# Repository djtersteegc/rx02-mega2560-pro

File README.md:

Mega 2560 Pro Embed version on [AK6DN's DEC RX02 emulator](https://github.com/AK6DN/rx02_emulator) board design and code.  There is a fork of his project at  https://github.com/djtersteegc/rx02_emulator that adds software support for this new board design. This was an exercise in how small I could make it while still using a Mega2560 shield and large'ish 0805 SMD parts for an easy DIY build.  If you are interested in a larger version built on a standard Arduino Mega 2560  with an LCD and buttons so you don't need to pick images via a serial/terminal connection, see my other project at https://github.com/djtersteegc/rx02-emulator-mega-shield.

Here's the two of them side by side on a Heathkit H11 for a size comparison.

See the VCFed thread at https://forum.vcfed.org/index.php?threads/building-the-worlds-currently-smallest-rx02-emulator.1240496/ for discussion or help with this project

# BOM

There is an interactive BOM at https://djtersteegc.github.io/rx02-mega2560-pro/ibom-v1.2.html  It's for a version 1.2 board which is hasn't been produced yet so ignore R32 and D4 which are for a power indicator LED if you are building a version 1.1 board.

C1 and C2 are bulk storage caps for the 5V rail, any value over 33uF should do.  C7 is a 47uF tantalum to prevent sag on the 3.3V rail when hot swapping the SD card since there is usually quite a bit of in rush current.  You can probably do without, especially if you never intend to hot swap since it's not really supported by the firmware.

The SD card connector is commonly available from several different Chinese suppliers and often called "long body", "non popping", or"push pull".  Here's some links on LCSC.

https://www.lcsc.com/product-detail/SD-Card-Connectors_Hanbo-Electronic-SD-112_C961673.html

https://www.lcsc.com/product-detail/SD-Card-Connectors_XUNPU-SD-102_C266602.html

https://www.lcsc.com/product-detail/SD-Card-Connectors_Megastar-ZX-SD-282-8Y_C7419835.html

It should also cross with a Wurth 693063010911 or AMP GSD090012SEU if you want something domestically.

You can also use BSS138 FET's in place of the 2N7002's.

# Assembly

This time around I used the same resistor references as AK6DN's original version so his resistor stuffing table is the same. Most of the resistor footprints should NOT be populated.

| Signal         | Resistor | Value   | Resistor | Value   |
| -------------- | -------- | ------- | -------- | ------- |
| RX_DMA_MODE_H  | R2       | -       | R3       | **390** |
| RX_AC_L        | R4       | **120** | R5       | -       |
| RX_OUT_L       | R6       | -       | R7       | -       |
| RX_SHIFT_L     | R8       | -       | R9       | -       |
| RX_12BIT_L     | R10      | **180** | R23      | **390** |
| RX_DATA_L      | R11      | **180** | R12      | **390** |
| RX_DONE_L      | R13      | -       | R14      | -       |
| RX_XFER_RQST_L | R15      | -       | R16      | -       |
| RX_INIT_L      | R17      | -       | R18      | **390** |
| RX_ERROR_L     | R19      | -       | R20      | -       |
| RX_RUN_L       | R21      | **180** | R22      | **390** |

Assemble the top side first.

Then flip in over and do the bottom.  Followed by the headers and then the 40 pin connector. For the LED's, I first insert them in the PCB, then the PCB in the case, flip it over and support the case ~1mm off the work surface for the LED's to just poke through the top and get a nice reveal. Solder one leg on the LED's, flip it over to check your spacing again, and then solder the other leg.

# Case

Make sure to print two copies of the buttons. Angle the board in connector side first and it should drop in.  It's a snap fit design, so no screws needed to assemble.

# Flashing and Usage

See instructions at https://github.com/djtersteegc/rx02_emulator

# Getting a Board

If you are in the US, hit me up on the [VCFed thread](https://forum.vcfed.org/index.php?threads/building-the-worlds-currently-smallest-rx02-emulator.1240496/) above and if I still have extras, I can drop one in the mail for a couple of bucks. Otherwise, grab the gerbers and fab your own.

# Hardware Revisions

### Version 1.0

Required bodge wires since I failed to pick interrupt enabled pins on the Mega2560 for the RX_INIT and RX_RUN lines when I reamapped the pins to better fit this layout.

### Versions 1.1 (Current)

Working

### Version 1.2 (Not Produced Yet)

Added a power LED

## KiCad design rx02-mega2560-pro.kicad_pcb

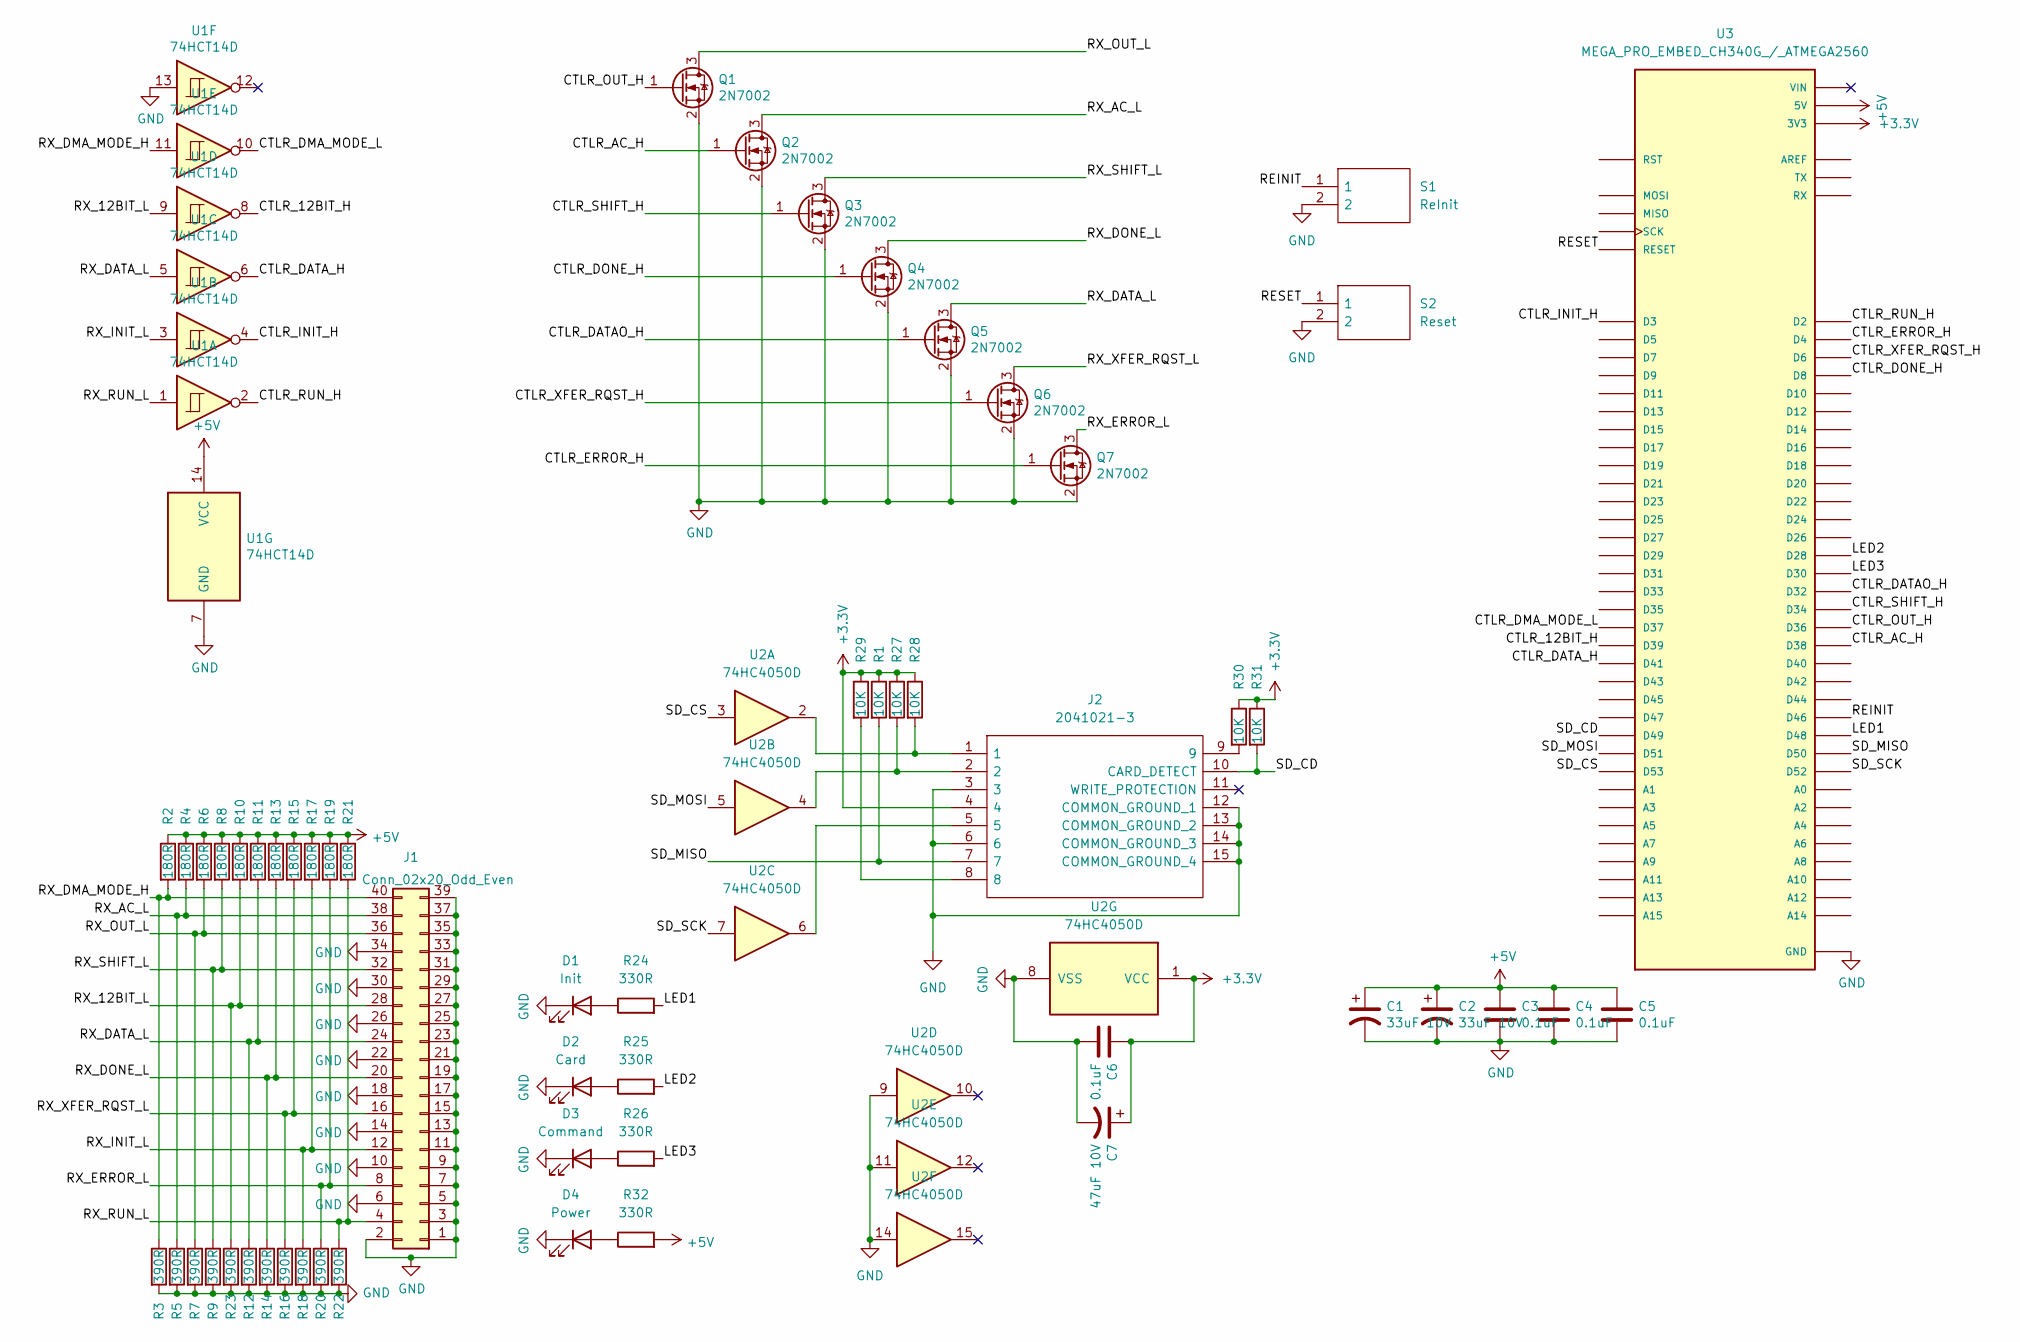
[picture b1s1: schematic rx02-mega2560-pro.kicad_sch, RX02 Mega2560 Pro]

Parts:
C1, C2: 33uF 10V; CP_Elec_5x5.8
C3, C4, C5, C6: 0.1uF; C_0805_2012Metric_Pad1.18x1.45mm_HandSolder
C7: 47uF 10V; CP_EIA-3528-12_Kemet-T_Pad1.50x2.35mm_HandSolder
D1: Init; LED_D3.0mm
D2: Card; LED_D3.0mm
D3: Command; LED_D3.0mm
D4: Power; LED_0805_2012Metric_Pad1.15x1.40mm_HandSolder
J1: Conn_02x20_Odd_Even; IDC-Header_2x20_P2.54mm_Horizontal
J2: 2041021-3; 2041021-3_2; Manufacturer_Part_Number 2041021-3; Mouser Part Number 571-2041021-3
Q1, Q2, Q3, Q4, Q5, Q6, Q7: 2N7002; SOT-23
R1, R27, R28, R29, R30, R31: 10K; R_0805_2012Metric_Pad1.20x1.40mm_HandSolder
R2, R4, R6, R8, R10, R11, R13, R15, R17, R19, R21: 180R; R_0805_2012Metric_Pad1.20x1.40mm_HandSolder
R3, R5, R7, R9, R12, R14, R16, R18, R20, R22, R23: 390R; R_0805_2012Metric_Pad1.20x1.40mm_HandSolder
R24, R25, R26, R32: 330R; R_0805_2012Metric_Pad1.20x1.40mm_HandSolder
S1: ReInit; SW_Push_SPST_NO_Alps_SKRK; Manufacturer_Part_Number SKRKAEE020; Mouser Part Number 688-SKRKAEE020
S2: Reset; SW_Push_SPST_NO_Alps_SKRK; Manufacturer_Part_Number SKRKAEE020; Mouser Part Number 688-SKRKAEE020
U1: 74HCT14D; SOIC-14_3.9x8.7mm_P1.27mm
U2: 74HC4050D; SOIC-16_3.9x9.9mm_P1.27mm
U3: MEGA_PRO_EMBED_CH340G_/_ATMEGA2560; MODULE_MEGA_PRO_EMBED_CH340G___ATMEGA2560; PARTREV 12/May/2017

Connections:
+3V3: C6.1, C7.1, J2.4, R1.1, R27.1, R28.1, R29.1, R30.1, R31.1, U2.1 (VCC), U3.3V3_1 (3V3), U3.3V3_2 (3V3)
+5V: C1.1, C2.1, C3.1, C4.1, C5.1, R2.1, R4.1, R6.1, R8.1, R10.1, R11.1, R13.1, R15.1, R17.1, R19.1, R21.1, R32.2, U1.14 (VCC), U3.5V_1 (5V), U3.5V_2 (5V), U3.5V_3 (5V)
/CTLR_12BIT_H: U1.8, U3.D39
/CTLR_AC_H: Q2.1 (G), U3.D38
/CTLR_DATAO_H: Q5.1 (G), U3.D32
/CTLR_DATA_H: U1.6, U3.D41
/CTLR_DMA_MODE_L: U1.10, U3.D37
/CTLR_DONE_H: Q4.1 (G), U3.D8
/CTLR_ERROR_H: Q7.1 (G), U3.D4
/CTLR_INIT_H: U1.4, U3.D3
/CTLR_OUT_H: Q1.1 (G), U3.D36
/CTLR_RUN_H: U1.2, U3.D2
/CTLR_SHIFT_H: Q3.1 (G), U3.D34
/CTLR_XFER_RQST_H: Q6.1 (G), U3.D6
/LED1: R24.2, U3.D48
/LED2: R25.2, U3.D28
/LED3: R26.2, U3.D30
/REINIT: S1.1, U3.D46
/RESET: S2.1, U3.RESET
/RX_12BIT_L: J1.28, R10.2, R23.1, U1.9
/RX_AC_L: J1.38, Q2.3 (D), R4.2, R5.1
/RX_DATA_L: J1.24, Q5.3 (D), R11.2, R12.1, U1.5
/RX_DMA_MODE_H: J1.40, R2.2, R3.1, U1.11
/RX_DONE_L: J1.20, Q4.3 (D), R13.2, R14.1
/RX_ERROR_L: J1.8, Q7.3 (D), R19.2, R20.1
/RX_INIT_L: J1.12, R17.2, R18.1, U1.3
/RX_OUT_L: J1.36, Q1.3 (D), R6.2, R7.1
/RX_RUN_L: J1.4, R21.2, R22.1, U1.1
/RX_SHIFT_L: J1.32, Q3.3 (D), R8.2, R9.1
/RX_XFER_RQST_L: J1.16, Q6.3 (D), R15.2, R16.1
/SD_CD: J2.10 (CARD_DETECT), R31.2, U3.D49
/SD_CS: U2.3, U3.D53
/SD_MISO: J2.7, R1.2, U3.D50
/SD_MOSI: U2.5, U3.D51
/SD_SCK: U2.7, U3.D52
GND: C1.2, C2.2, C3.2, C4.2, C5.2, C6.2, C7.2, D1.1 (K), D2.1 (K), D3.1 (K), D4.1 (K), J1.1, J1.2, J1.3, J1.5, J1.6, J1.7, J1.9, J1.10, J1.11, J1.13, J1.14, J1.15, J1.17, J1.18, J1.19, J1.21, J1.22, J1.23, J1.25, J1.26, J1.27, J1.29, J1.30, J1.31, J1.33, J1.34, J1.35, J1.37, J1.39, J2.3, J2.6, J2.12 (COMMON_GROUND_1), J2.13 (COMMON_GROUND_2), J2.14 (COMMON_GROUND_3), J2.15 (COMMON_GROUND_4), Q1.2 (S), Q2.2 (S), Q3.2 (S), Q4.2 (S), Q5.2 (S), Q6.2 (S), Q7.2 (S), R3.2, R5.2, R7.2, R9.2, R12.2, R14.2, R16.2, R18.2, R20.2, R22.2, R23.2, S1.2, S2.2, U1.7 (GND), U1.13, U2.8 (VSS), U2.9, U2.11, U2.14, U3.GND_1 (GND), U3.GND_2 (GND), U3.GND_3 (GND)
unnamed: D1.2 (A), R24.1
unnamed: D2.2 (A), R25.1
unnamed: D3.2 (A), R26.1
unnamed: D4.2 (A), R32.1
unnamed: J2.1, R28.2, U2.2
unnamed: J2.2, R27.2, U2.4
unnamed: J2.5, U2.6
unnamed: J2.8, R29.2
unnamed: J2.9, R30.2

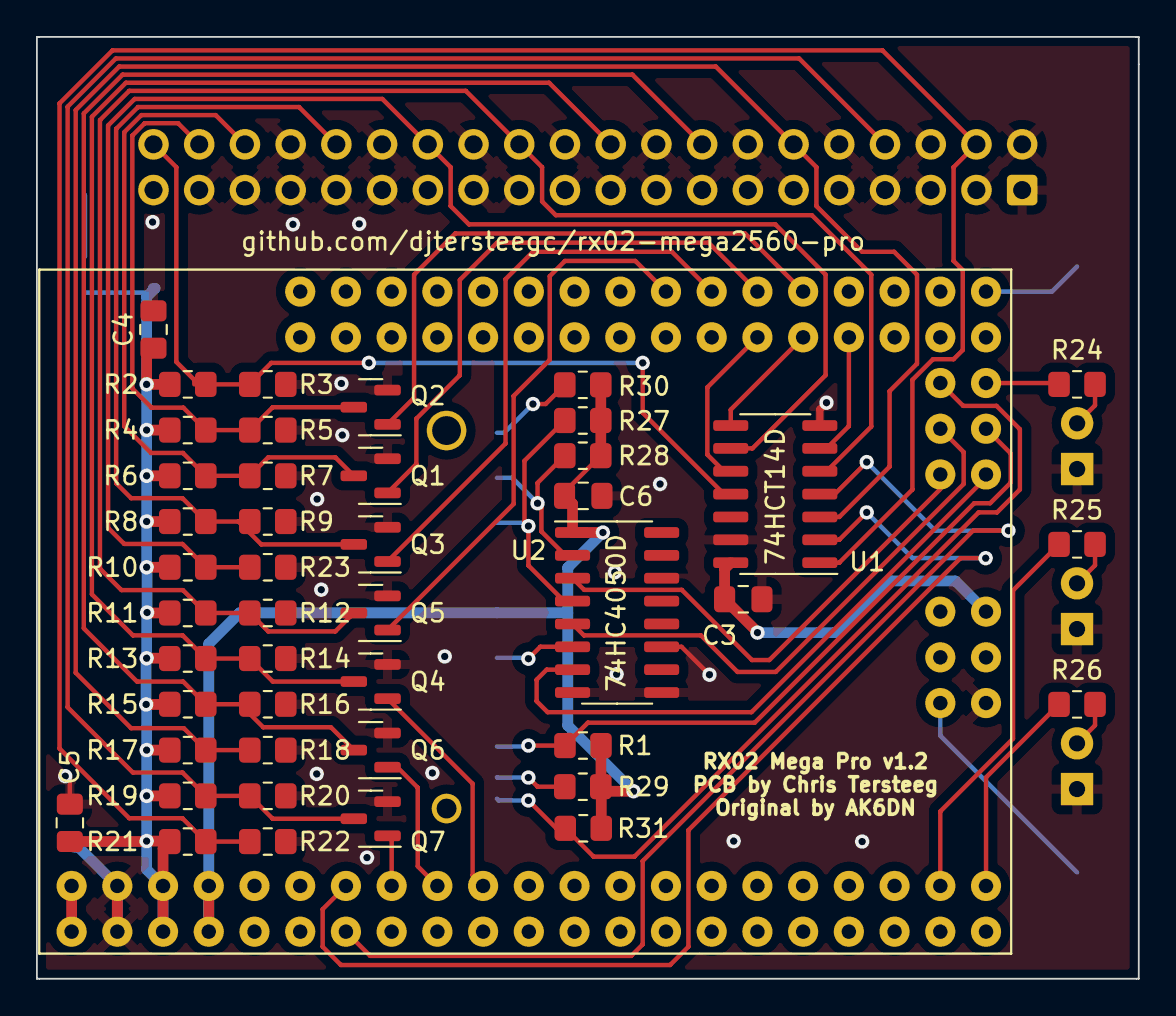
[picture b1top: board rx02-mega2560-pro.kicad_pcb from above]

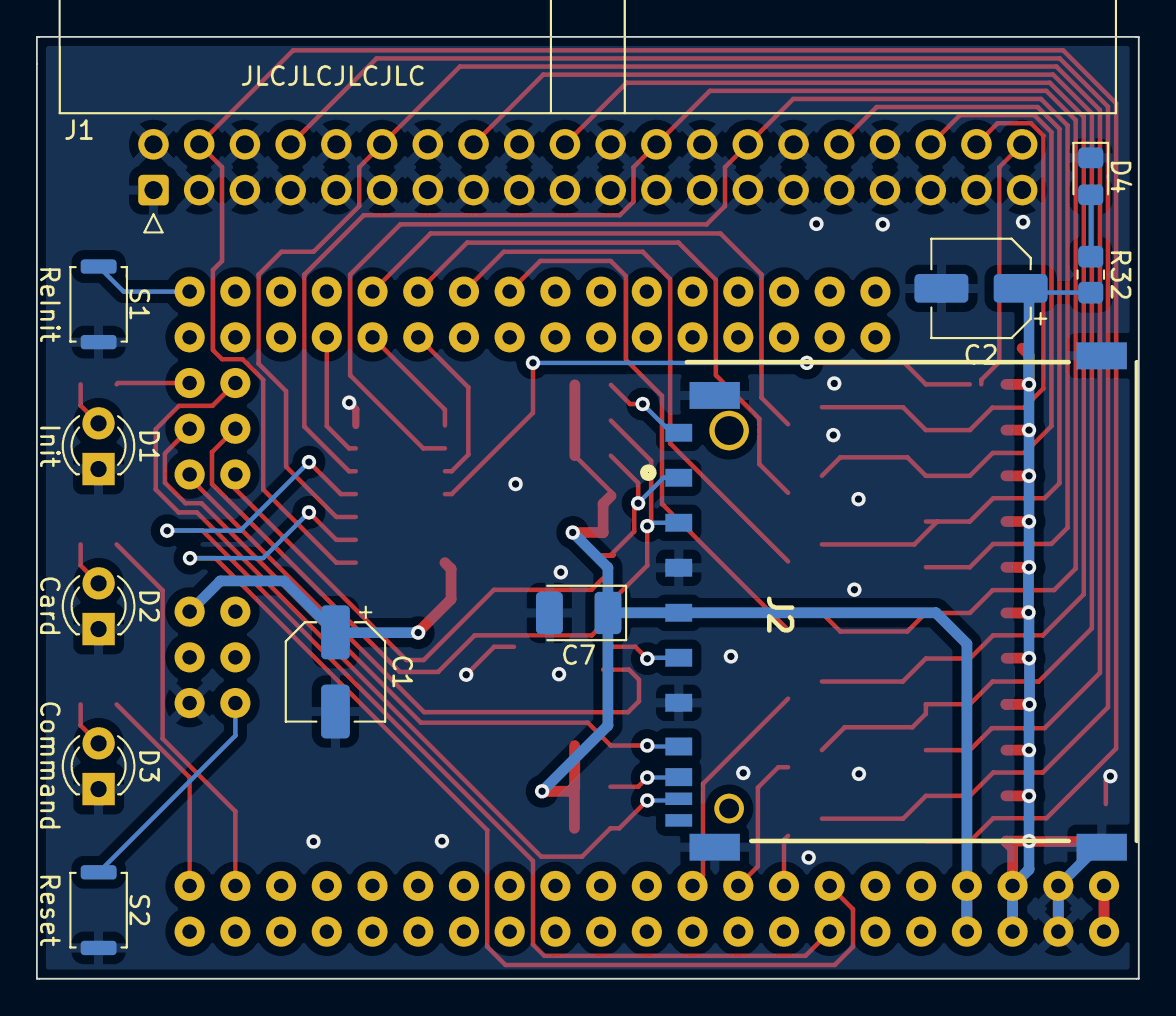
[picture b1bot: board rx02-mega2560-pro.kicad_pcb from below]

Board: 2 copper layers, 61.2 x 52.3 mm, 57 parts (12 on the bottom side), 45 nets.

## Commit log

2023-09-22 Add pin mapping file
2023-11-12 Update to v1.2, add some more docs
2023-11-13 Add termination resistor table
2023-11-13 Update docs
2023-11-13 Resize pics
2023-11-27 Remove extra PCB stops in body that prevented the insertion of board at an angle
2023-11-27 Update PIN Mappings for boards types
2025-02-28 Reorganize case files and add STEP exports
